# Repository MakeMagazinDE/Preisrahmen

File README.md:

Maker Media GmbH

***

# Preisrahmen

**Wer einen dynamischen Strompreisvertrag wählt, bekommt vom Energielieferanten keine festen kWh-Preise mehr, sondern stündlich wechselnde Tarife. Um die günstigsten Stunden optimal zu nutzen, haben wir unseren Preisrahmen entwickelt. Täglich ruft er die für den nächsten Tag festgelegten Preise ab und zeigt sie auf seinem ePaper-Display an.**

Der vollständige Artikel zum Projekt erscheint in der Make 4/24.

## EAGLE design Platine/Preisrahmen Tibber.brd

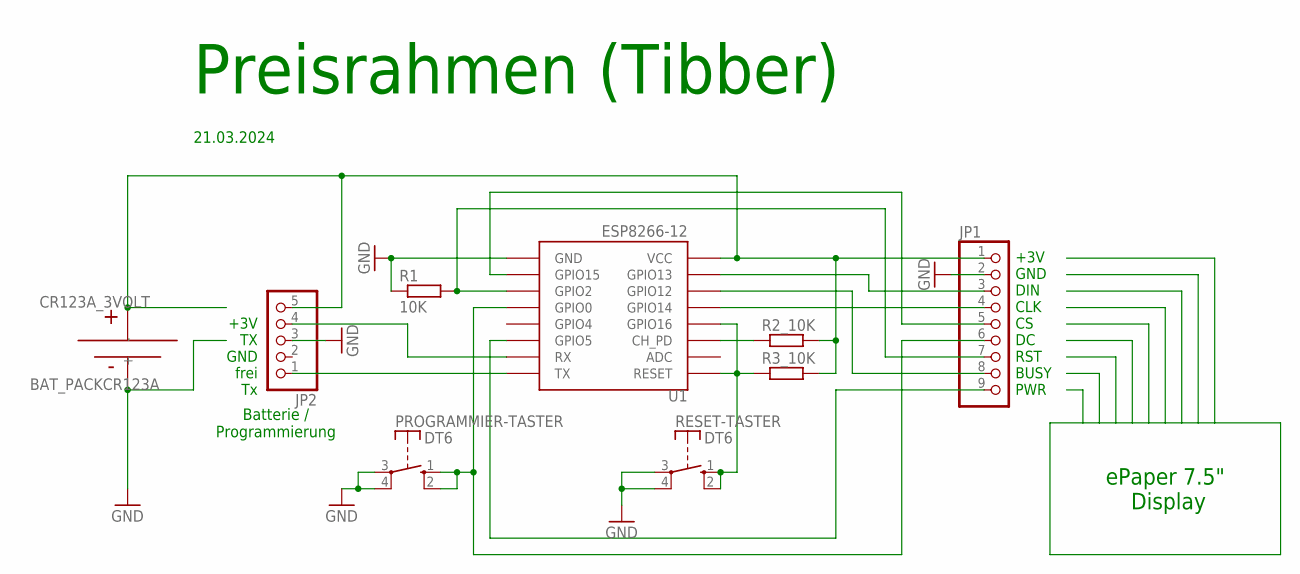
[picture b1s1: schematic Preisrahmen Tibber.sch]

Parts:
CR123A_3VOLT: BAT_PACKCR123A; BH123A
JP1: PINHD-1X9/90; 1X09/90
JP2: PINHD-1X5/90; 1X05/90
PROGRAMMIER-TASTER: DT6
R1: 10K; 0207/7
R2_10K, R3_10K: R-EU_0207/7; 0207/7
RESET-TASTER: DT6
U1: ESP8266-12; ESP12

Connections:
GND: CR123A_3VOLT.-, JP1.2, JP2.3, PROGRAMMIER-TASTER.3, PROGRAMMIER-TASTER.4, R1.1, RESET-TASTER.3, RESET-TASTER.4, U1.GND
unnamed: R2_10K.1, U1.CH_PD
unnamed: R3_10K.1, RESET-TASTER.1 (S), RESET-TASTER.2 (S), U1.GPIO16, U1.RESET
unnamed: JP1.7, R1.2, U1.GPIO2
unnamed: JP1.6, PROGRAMMIER-TASTER.1 (S), PROGRAMMIER-TASTER.2 (S), U1.GPIO0
unnamed: JP2.1, U1.TX
unnamed: JP2.4, U1.RX
unnamed: JP1.9, U1.GPIO5
unnamed: JP1.3, U1.GPIO13
unnamed: JP1.4, U1.GPIO14
unnamed: JP1.5, U1.GPIO15
unnamed: CR123A_3VOLT.+, JP1.1, JP2.5, R2_10K.2, R3_10K.2, U1.VCC
unnamed: JP1.8, U1.GPIO12

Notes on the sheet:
Preisrahmen (Tibber)
21.03.2024
+3V TX GND frei Tx
+3V GND DIN CLK CS DC RST BUSY PWR
ePaper 7.5" Display
Batterie / Programmierung

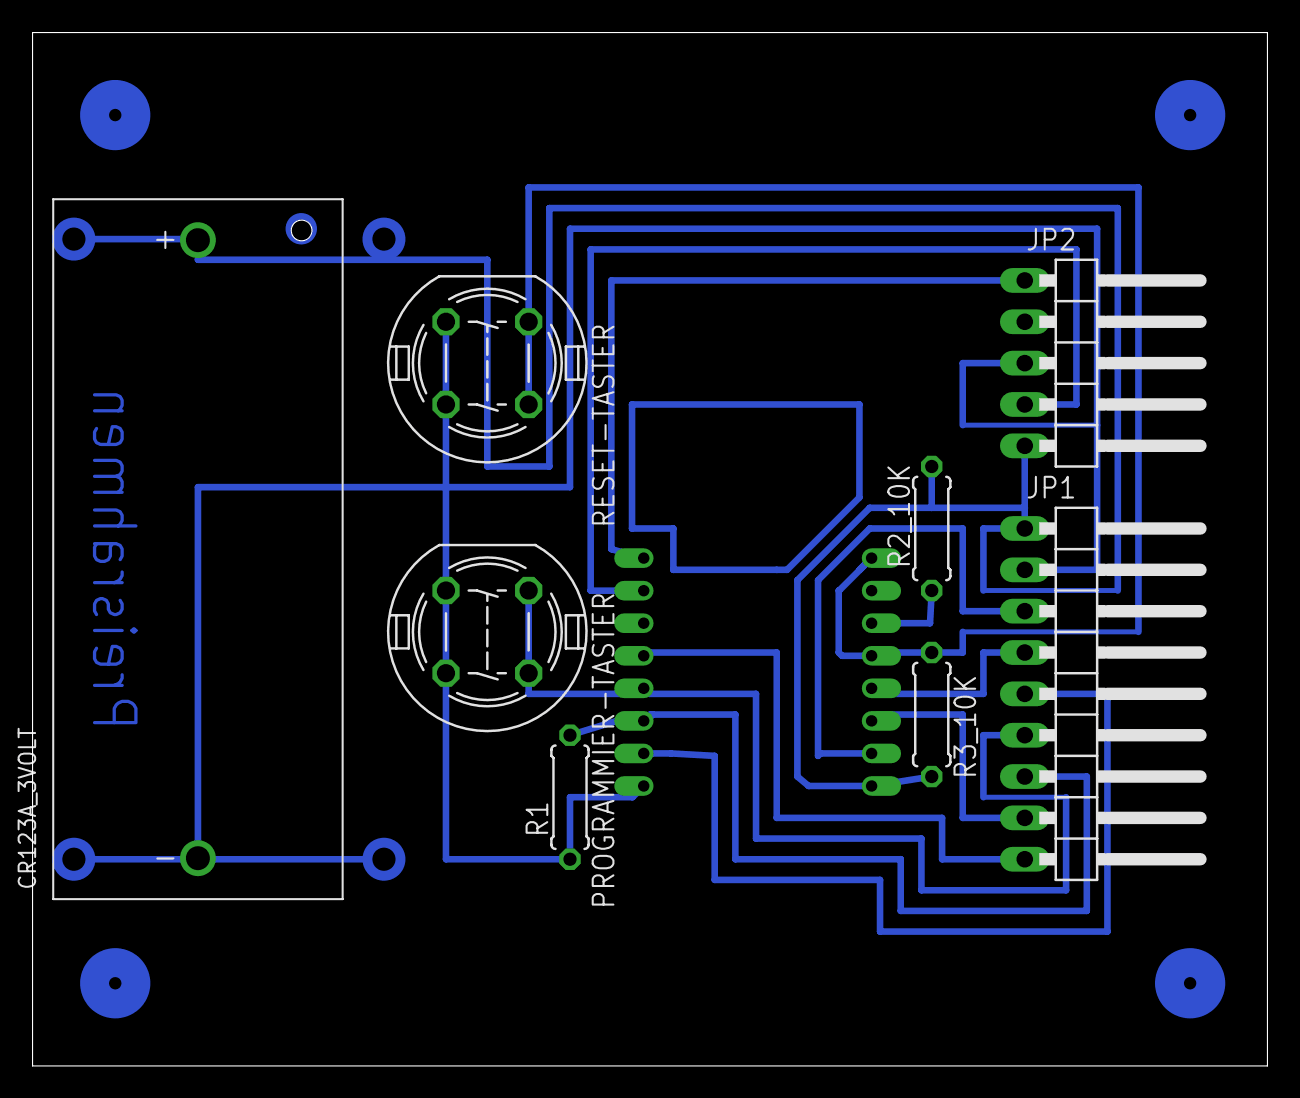
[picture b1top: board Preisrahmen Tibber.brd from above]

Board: 2 copper layers, 75.9 x 63.5 mm, 9 parts (1 on the bottom side), 13 nets.

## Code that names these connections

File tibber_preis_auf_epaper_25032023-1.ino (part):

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#define ENABLE_GxEPD2_GFX 0  //wenn ohne Grauwerte
#include <GxEPD2_BW.h> 
#define GxEPD_LIGHTGREY GxEPD_BLACK
//Pins ePapaer an ESP8266: VCC=gr=3,3V, GND=br=GND, DIN=bl=Gpio13=D7=MOSI, CLK=ge=D5=Gpio14=SCLK, CS=or=D8=Gpio15=CS, DC=gn=D3=Gpio0, RST=ws=D4=Gpio2, BUSY=vi=D6=Gpio12=MISO, PWR=rt=3,3V
GxEPD2_DISPLAY_CLASS<GxEPD2_DRIVER_CLASS, MAX_HEIGHT(GxEPD2_DRIVER_CLASS)> display(GxEPD2_DRIVER_CLASS(/*CS=D8*/ EPD_CS, /*DC=D3*/ 0, /*RST=D4*/ 2, /*BUSY=D2*/ 4));
#include <Fonts/FreeMonoBold9pt7b.h>
//############### ePaper "Gedoens" Ende ######################################################
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#include <time.h>
#include "ota.h" 
#include "Internetzeit.h"
#define ePaper_on 5 //D1 = GPIo5
#define LED 2 //D4
#define AN LOW
#define AUS HIGH
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
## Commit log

2024-06-25 Create w
2024-06-25 Create a
2024-08-12 Add files via upload
    Der Schaltplan wurde um einen fehlenden Widerstand ergänzt.
2024-08-14 Add files via upload
    Dies ist eine neue, korrigierte Version des Halterahmens. In der alten Version war der Bereich für das ePaper fälschlicherweise bedruckt.
